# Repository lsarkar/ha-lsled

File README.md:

## LS LEDS

## Folder structure
### custom_components/ls_leds

Home Assistant Custom Component for integrating WS2812 LED Strips with custom firmware that receives UDP commands

### kitchenleds
Raspberry Pi Pico W python code

## Installation
- Install ls_leds custom component through HACS (Home Assistant Community Store)
- Update Home Assistant YAML configuration

```
light:
  - platform: ls_leds
    host: <ip address>
    port: <port>
```

ip address - static IP address of the WS2812B light strip
port - The default port is **2522**

### TODOs
- Add config flow using reference thread: https://community.home-assistant.io/t/custom-integration-error-creating-device-with-entities/635842/8
- Add custom read commands with UDP packet payload

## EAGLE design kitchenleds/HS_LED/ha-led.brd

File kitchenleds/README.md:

Kitchen LED project with button switch to change colors of the LED strip. Communication to done over UDP

###  Hardware
Code runs on the Pi Pico W with MicroPython

The Pi Pico W listens for UDP messages on port 2252

--------
### BOM
| Item | Quantity |
| -- | -- |
| [Raspberry Pi Pico W](https://www.adafruit.com/product/5526?gclid=CjwKCAiA3KefBhByEiwAi2LDHHrzBphUm--6PniyvxpFsNIY99liun2cfvlbB1_9122XP3Poi4Q0pxoCPsEQAvD_BwE) | 1 |
| [74AHC125 Level Converter](https://cdn-shop.adafruit.com/product-files/1787/1787AHC125.pdf) | 1 |
| [WS2812B LED Strip](https://www.amazon.com/ALITOVE-Individual-Addressable-Programmable-Non-Waterproof/dp/B086B8Z6BK/ref=sr_1_10?crid=X51V29C4HMQV&keywords=ws2812b&qid=1676341262&sprefix=ws2812b%2Caps%2C194&sr=8-10&th=1) | 2 |

---

### Wiring
LED Strips are connected to GP27 and GP28 on the Pi Pico

The Level Converter is required as the GPIOs from the Pico output 3.3V and the WS2812 LED strips require 5V

<b>Indexes</b>
<p>
0 - both strips
1 - upper strip
2 - lower strip
</p>

---

### Useful Links
- [Pico W Pin Out Diagram](https://datasheets.raspberrypi.com/picow/PicoW-A4-Pinout.pdf)
- [Level Converter Wiring Example](https://www.adafruit.com/product/1787)
- [WLAN reference](https://docs.micropython.org/en/latest/library/network.WLAN.html)

- https://how2electronics.com/iot-rgb-led-strip-control-with-raspberry-pi-pico-w/
- https://how2electronics.com/raspberry-pi-pico-w-web-server-tutorial-with-micropython/

- https://github.com/pi3g/pico-w/blob/main/MicroPython/I%20Pico%20W%20LED%20web%20server/main.py

- [Async Webserver](https://gist.github.com/aallan/3d45a062f26bc425b22a17ec9c81e3b6)

- https://datasheets.raspberrypi.com/picow/connecting-to-the-internet-with-pico-w.pdf

### TODOs
- Add config flow using reference thread: https://community.home-assistant.io/t/custom-integration-error-creating-device-with-entities/635842/8
- Add custom read commands with UDP packet payload

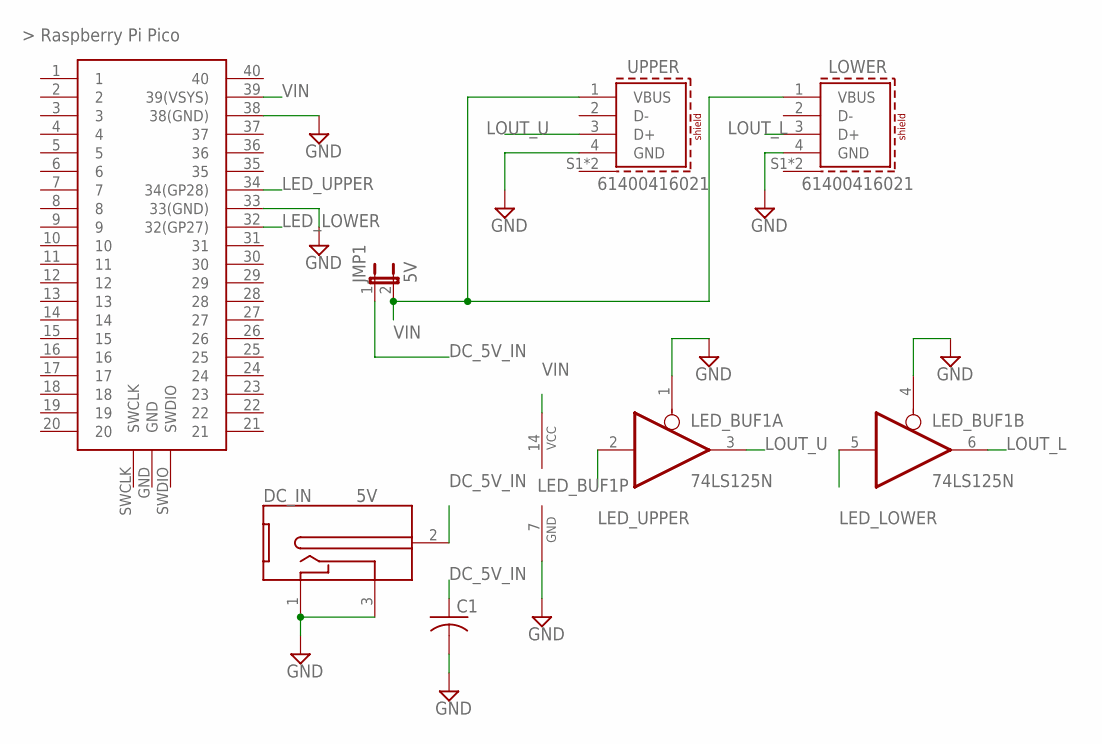
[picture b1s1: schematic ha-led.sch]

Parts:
C1: C-US025-030X050; C025-030X050
DC_IN: 5V; DC-21MM
JMP1: 5V; JP1
LED_BUF1: 74LS125N; DIL14
LOWER: 61400416021
U$1: RASPBERRY-PI-PICO_TH; FT_RASPBERRY-PI-PICO_TH
UPPER: 61400416021

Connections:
DC_5V_IN: C1.1, DC_IN.2 (3), JMP1.1
GND: C1.2, DC_IN.1, DC_IN.3 (2), LED_BUF1.1 (OE), LED_BUF1.4 (OE), LED_BUF1.7 (GND), LOWER.4 (GND), U$1.33 (33(GND)), U$1.38 (38(GND)), UPPER.4 (GND)
LED_LOWER: LED_BUF1.5 (I), U$1.32 (32(GP27))
LED_UPPER: LED_BUF1.2 (I), U$1.34 (34(GP28))
LOUT_L: LED_BUF1.6 (O), LOWER.3 (D+)
LOUT_U: LED_BUF1.3 (O), UPPER.3 (D+)
VIN: JMP1.2, LED_BUF1.14 (VCC), LOWER.1 (VBUS), U$1.39 (39(VSYS)), UPPER.1 (VBUS)

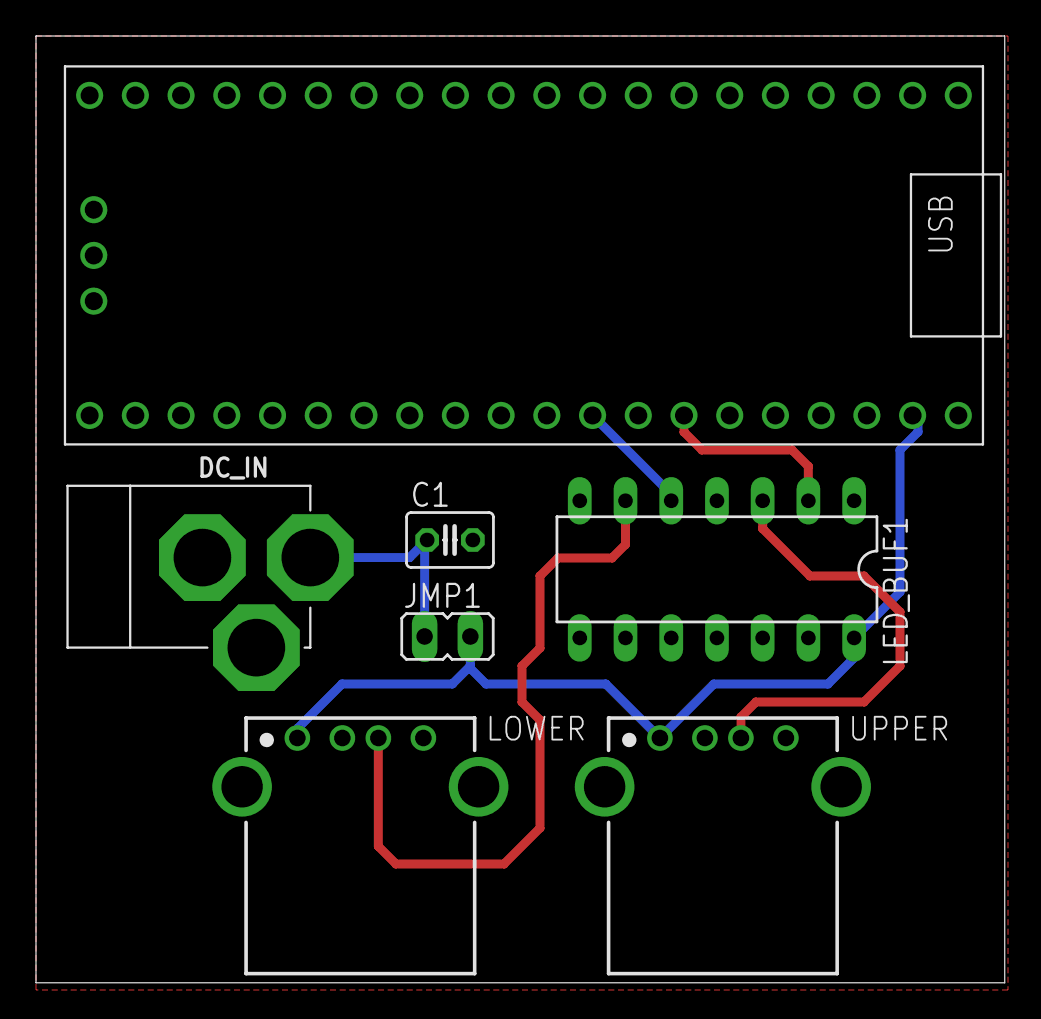
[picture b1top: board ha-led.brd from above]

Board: 2 copper layers, 53.8 x 52.6 mm, 7 parts (0 on the bottom side), 7 nets.

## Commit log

2024-04-21 Feat: Add basic light strip integration
2024-04-21 Remove redundant files
2024-04-23 Chore: Add folder to match expected custom component layout
2024-04-29 Feat: Add ip address and port configuration to YAML
2024-04-29 Chore: Remove deprecated use of SUPPORTED_FEATURES
2024-04-29 Chore[README]: Update reference links
2024-05-03 Chore[const]: Add const file for static variables
2024-05-04 Feat: Add kitchen led pico project
2024-05-07 Feat: Add read back RGB state from pico
2024-05-08 Fix: Set initial state for lower and upper strips
2024-05-08 Chore[README]: Add folder structure info
2024-05-08 Chore: Add database file for packetsender
2024-05-13 Feat[light]: Add ability to get light state from device
2024-05-14 Chore: Code clean up and add boilerplate test
2024-11-30 Feat: Add ConfigFlow for IP configuration
2024-12-01 Refac: Remove legacy methods
2024-12-01 Feat: Add state property
2024-12-02 Refac: Move ip address validation to udp class
2024-12-02 Feat: Add udp async send method
2024-12-02 Chore: Remove deprecated method
2024-12-03 Feat: Add async_turn_off light method
2024-12-07 Chore: Simplify packet creation
2024-12-07 Feat: Update flow to include ip address and ip port configuration
2024-12-08 Test: Add hassfest validation
2024-12-08 Chore: Add hacs.json
2024-12-08 Refac: Move rgb packet creation to datapacket
2025-03-09 Feat: Add schematic and board files
2025-03-30 Chore[pico/main.py]: Minor tweaks

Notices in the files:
parts and their libraries:
Wurth_Connectors_WR-USB: Copyright: Würth Elektronik
